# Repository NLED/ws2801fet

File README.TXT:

THERE IS NO WARRANTY FOR THE PROGRAM, TO THE EXTENT PERMITTED BY APPLICABLE LAW. 
EXCEPT WHEN OTHERWISE STATED IN WRITING THE COPYRIGHT HOLDERS AND/OR OTHER PARTIES 
PROVIDE THE PROGRAM “AS IS” WITHOUT WARRANTY OF ANY KIND, EITHER EXPRESSED OR IMPLIED,
INCLUDING, BUT NOT LIMITED TO, THE IMPLIED WARRANTIES OF MERCHANTABILITY AND FITNESS 
FOR A PARTICULAR PURPOSE. THE ENTIRE RISK AS TO THE QUALITY AND PERFORMANCE OF THE 
PROGRAM IS WITH YOU. SHOULD THE PROGRAM PROVE DEFECTIVE, YOU ASSUME THE COST OF ALL 
NECESSARY SERVICING, REPAIR OR CORRECTION.

 Original Author: Jeffrey Nygaard
 Company: Northern Lights Electronic Design, LLC
 Date: July 26, 2018
 Contact: JNygaard@NLEDshop.com
 Copyright© 2018 by Northern Lights Electronic Design, LLC. All Rights Reserved
 
;=============          www.NLEDShop.com/ws2801fet          ============
;=============     www.NorthernLightsElectronicDesign.com       ============

This work is licensed under a Attribution-NonCommercial 4.0 International (CC BY-NC 4.0)
https://creativecommons.org/licenses/by-nc/4.0/legalcode

Free to use for personal use, but please attribute the original author.

Commercial licenses versions are available for a donation of any amount. Contact JNygaard@NLEDshop.com for details.

================================================================================================================

Ready-made devices are available for purchase, and large batch manufacturing of any device can be requested.
Please see the webpage www.NLEDShop.com/ws2801fet

NLED is available for custom design and manufacturing, please contact via phone or email to discuss your project.

================================================================================================================

Minimum Input Voltage: 5 volts
Maximum Input Voltage: 24 volts
Current Consumption: < 30mA estimated

BOM:
1x WS2801SO - SOIC-16
3x NTD5867NLT4G - TO-252-4 - N-Chan MOSFET, low RDS
1x 742C083103JP - 0603-ARV - quad 10Kohm network resistor
1x UA78M05CDCYR - SOT-223-4 - 5 volt regulator, many other equivalents
2x 50 ohm resistor - 0805 - for signal integrity
2x 10uF >=16vdc - 0805
1x 0.1uF >=6.3vdc - 0805
2x 2-pin 5.08 spaced screw terminal
1x 4-pin 5.08 spaced screw terminal

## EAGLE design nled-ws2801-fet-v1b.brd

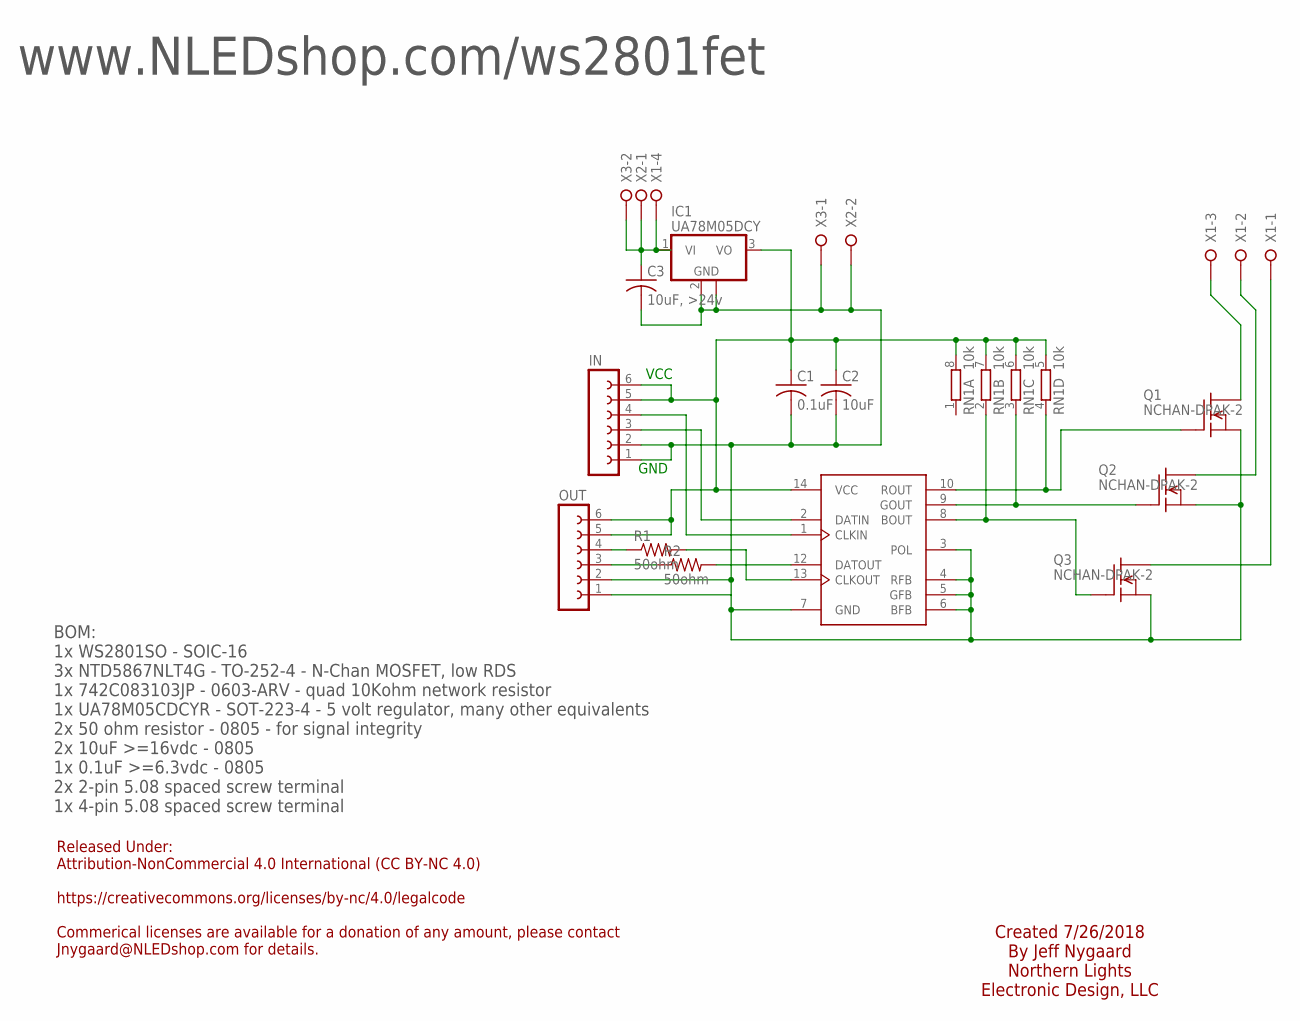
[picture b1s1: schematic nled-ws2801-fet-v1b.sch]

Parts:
C1: 0.1uF; C1206
C2: 10uF; C1206
C3: 10uF, >24v; C1206
IC1: UA78M05DCY; SOT223
IN: FE06-1; FE06
OUT: FE06-1; FE06
Q1, Q2, Q3: NCHAN-DPAK-2; DPAK-2PIN
R1, R2: 50ohm; M0805
RN1: 10k; 0603-ARV
WS2801: WS2801; SOP14
X1: W237-04P; W237-4P
X2, X3: W237-02P; W237-132

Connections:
GND: C1.2, C2.2, C3.2, IC1.2 (GND), IC1.4 (GND), IN.1, IN.2, OUT.1, OUT.2, Q1.3 (S), Q2.3 (S), Q3.3 (S), WS2801.3 (POL), WS2801.4 (RFB), WS2801.5 (GFB), WS2801.6 (BFB), WS2801.7 (GND), X2.2, X3.1
unnamed: Q1.1 (G), RN1.4 (1), WS2801.10 (ROUT)
unnamed: C3.1, IC1.1 (VI), X1.4, X2.1, X3.2
unnamed: Q2.2 (D), X1.2
unnamed: IN.4, WS2801.1 (CLKIN)
unnamed: Q2.1 (G), RN1.3 (1), WS2801.9 (GOUT)
unnamed: Q3.1 (G), RN1.2 (1), WS2801.8 (BOUT)
unnamed: Q3.2 (D), X1.1
unnamed: OUT.4, R1.1
unnamed: IN.3, WS2801.2 (DATIN)
unnamed: R1.2, WS2801.13 (CLKOUT)
unnamed: R2.2, WS2801.12 (DATOUT)
unnamed: Q1.2 (D), X1.3
unnamed: OUT.3, R2.1
VCC: C1.1, C2.1, IC1.3 (VO), IN.5, IN.6, OUT.5, OUT.6, RN1.5 (2), RN1.6 (2), RN1.7 (2), RN1.8 (2), WS2801.14 (VCC)

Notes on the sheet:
VCC
GND
Released Under: Attribution-NonCommercial 4.0 International (CC BY-NC 4.0) https://creativecommons.org/licenses/by-nc/4.0/legalcode Commerical licenses are available for a donation of any amount, please contact Jnygaard@NLEDshop.com for details.
Created 7/26/2018 By Jeff Nygaard Northern Lights Electronic Design, LLC
BOM: 1x WS2801SO - SOIC-16 3x NTD5867NLT4G - TO-252-4 - N-Chan MOSFET, low RDS 1x 742C083103JP - 0603-ARV - quad 10Kohm network resistor 1x UA78M05CDCYR - SOT-223-4 - 5 volt regulator, many other equivalents 2x 50 ohm resistor - 0805 - for signal integrity 2x 10uF >=16vdc - 0805 1x 0.1uF >=6.3vdc -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
www.NLEDshop.com/ws2801fet

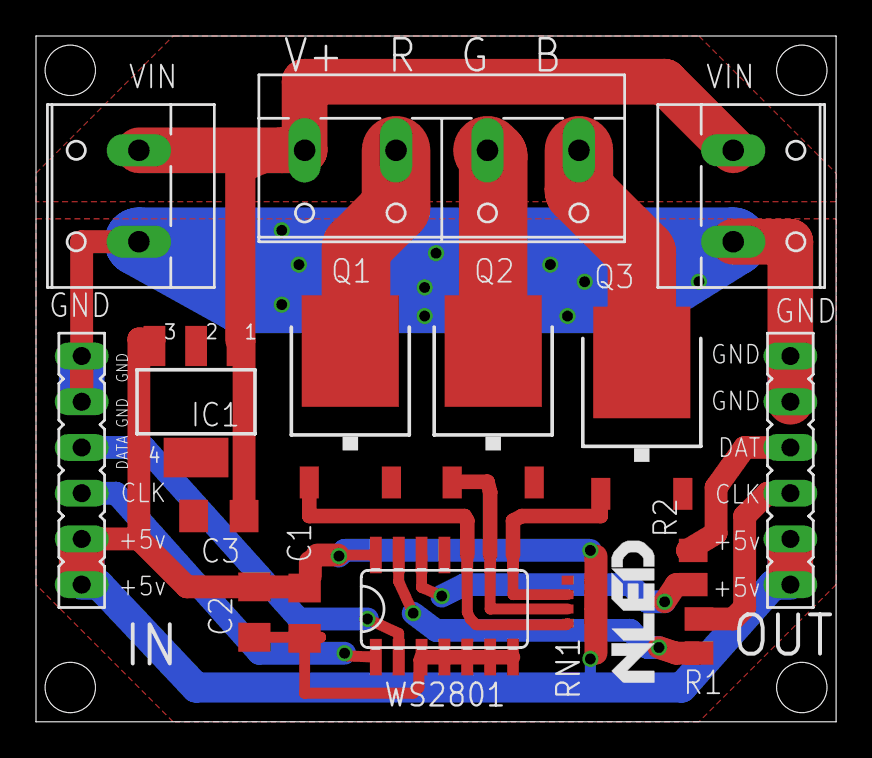
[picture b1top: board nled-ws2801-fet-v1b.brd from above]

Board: 4 copper layers, 44.5 x 38.1 mm, 16 parts (0 on the bottom side), 15 nets.

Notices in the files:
nled-ws2801-fet-v1b.brd:
Copyright 2017
